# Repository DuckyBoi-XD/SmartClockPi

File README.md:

A Raspberry Pi Zero 2 W based smart clock with touchscreen display, environmental sensing, and internet weather integration.

## KiCad Stuff

This project uses KiCad for PCB design. The files are located in the `PCB/` directory. You can open them with KiCad to view the schematics and PCB layout. These are the screenshots of the PCB and schematics:

### PCB Design

### PCB rendering

### Schematics

## Sketch

## CAD (case design)

## BOM (table format)

| Component | Description | Quantity | Link | Price | Shipping | Est. price (exl. GST) | Est. price (inc. GST) |
|-----------|-------------|----------|------|-------|----------|------------------------|------------------------|
| Raspberry Pi Zero 2 W | Main controller/computer of the project | 1 | https://www.aliexpress.com/item/1005007899652009.html | $15.00 | $0.00 | $15.00 | $17.25 |
| ILI9488 3.5" SPI TFT Touchscreen | 480x320 pixel color LCD with resistive touch input, using SPI interface; displays the clock and all UI elements. | 1 | https://www.aliexpress.com/item/1005007096645415.html | $12.34 | $0.00 | $12.34 | $14.19 |
| DHT22 Sensor | provides indoor environmental readings | 1 | https://www.aliexpress.com/item/32759901711.html | $2.05 | $0.00 | $2.05 | $2.36 |
| 1x14 Pin Socket Header | Single-row, female 2.54mm pitch header; connects the TFT display module to the PCB. | 1 (pack of 10, use 1) | https://www.aliexpress.com/item/4001198421663.html | $1.99 | $0.00 | $1.99 | $2.29 |
| 1x6 Pin Socket Header | Single-row, female 2.54mm pitch header; connects the DAC to the PCB. | 1 (pack of 10, use 1) | https://www.aliexpress.com/item/4001198421663.html | $1.70 | $0.00 | $1.70 | $1.96 |
| 1x6 Pin Socket Header Right angled | Single-row, female 2.54mm pitch, right angle header; connects the RTC module to the PCB. | 1 (pack of 5, use 1) | https://www.aliexpress.com/item/1005008210852764.html | $1.64 | $0.00 | $1.64 | $1.89 |
| 1x4 Pin Socket Header | Single-row, female 2.54mm pitch header; connects the DHT22 to the PCB. | 1 (pack of 10, use 1) | https://www.aliexpress.com/item/4001198421663.html | $1.69 | $0.00 | $1.69 | $1.94 |
| Photoresistor | for automatic display brightness adjustment. 5528 | 1 (pack of 50, use 1) | https://www.aliexpress.com/item/1005002145052802.html | $1.66 | $1.68 | $3.34 | $3.84 |
| MCP3008 (DIP) | 8-channel, 10-bit ADC with SPI interface; reads analog sensors like photoresistors. | 3 (use 1) | https://www.digikey.co.nz/en/products/detail/microchip-technology/MCP3008-I-P/319422 | $9.36 | $0.00 | $9.36 | $10.76 |
| DS3231 RTC (module) | Real-time clock module with battery backup; keeps accurate time when Pi is powered off (or when my internet connection dies) | 1 | https://www.aliexpress.com/item/1005008172587774.html | $1.70 | $0.00 | $1.70 | $1.96 |
| DIP-16 IC socket | For MCP3008 (DIP) | 1 (pack of 10, use 1) | https://www.aliexpress.com/item/1005009030108697.html | $0.60 | $1.63 | $2.23 | $2.56 |
| LIR3032 cell | 3.6V Lithium Battery Rechargeable Battery | 1 (pack of 2, use 1) | https://www.aliexpress.com/item/1005009124669879.html | $7.17 | $0.00 | $7.17 | $8.25 |
| micro-USB port | Power input | 5 (use 1) | https://www.digikey.co.nz/en/products/detail/amphenol-cs-fci/10118193-0001LF/2785388 | $2.15 | $0.00 | $2.15 | $2.47 |
| USB-A port | Power output (from battery charger) | 5 (use 1) | https://www.digikey.co.nz/en/products/detail/gct/USB1046-GF-0190-L-B-A/10649632 | $3.65 | $0.00 | $3.65 | $4.20 |
| 18650 Lithium Battery Charger | 5V 2.4A Dual USB OUT | 1 (pack of 2, use 1) | https://www.aliexpress.com/item/1005006839030660.html | $6.77 | $0.00 | $6.77 | $7.79 |
| microSD card | 64GB | 2 (use 1) | https://www.digikey.co.nz/en/products/detail/raspberry-pi/SC1629/24627140 | $12.98 | $0.00 | $12.98 | $14.93 |
| Diode | 1N4001 | 100 | https://www.digikey.co.nz/en/products/detail/diotec-semiconductor/1N4001/13164614 | $4.66 | $0.00 | $4.66 | $5.36 |
| USB speaker |  | 1 | https://www.aliexpress.com/item/1005007586786674.html | $4.52 | $8.20 | $12.72 | $14.63 |
| **TOTAL** |  |  |  |  |  | **$103.14** | **$118.61** |

## Why I Made This

I wanted a smart clock that could display the time, date, indoor temperature, humidity, and outdoor weather conditions. I also wanted it to have a touchscreen interface for easy interaction. The Raspberry Pi Zero 2 W was chosen for its compact size and sufficient processing power for this project.

"Why don't you just buy a pre-made smart clock?" you might ask. Well, I wanted to learn more about PCB layout/designing. This project is a great way to "exercise" while creating something useful for myself.

Also, I wanted to make it modular so I can easily swap out components or add new features in the future. The custom PCB design allows for easy connections and modifications.

## Features

### Display & Interface

- **3.5" ILI9488 SPI TFT Touchscreen** (480x320 pixels)
- Resistive touch input for UI
- Large, clear font display for time and date
- Automatic brightness adjustment via photoresistor (TO-DO, once I get the parts)

### Environmental Monitoring

- **DHT22 Sensor** for indoor temperature, humidity readings
- Real-time sensor data updates

### Weather Integration

- Internet weather data from wttr.in (Auckland, Half Moon Bay area)
- No API key required
- Displays outdoor temperature, humidity, and weather status
- Update every 10 minutes

### Time & Clock Features

- **DS3231 Real-Time Clock (RTC)** with battery backup
- Maintains accurate time even when Pi is powered off (or when my internet dies)
- Large, readable time display

### Hardware Features

- Custom PCB design with modular connections (so i can unplug and replug the modules)
- Female header pins for easy module connection
- Compact form factor (94.5mm x 67.2mm PCB)

## Hardware Components

Please see [SmartClockPi-bom.csv](SmartClockPi-bom.csv) (Created since this is required for Highway)

## Software Features

- **Python-based application** using:
  - `luma.lcd` for display control
  - `adafruit-circuitpython-bme280` for sensor interface
  - `Pillow` for graphics rendering
- Real-time clock display with large, clear fonts. Need to test if this actually works
- Weather data integration from wttr.in
- Environmental sensor monitoring

## Project Structure

```txt
SmartClockPi/
├── README.md
├── JOURNAL.md                # Development journal with progress updates
├── SmartClockPi-bom.csv      # Bill of Materials
├── PCB/                      # KiCad PCB design files
│   ├── smartclockpi.kicad_pro
│   ├── smartclockpi.kicad_sch
│   ├── smartclockpi.kicad_pcb
│   └── Gerber/               # Manufacturing files
└── [Software files to be added]
```

## Acknowledgements

- Thanks to the Raspberry Pi community for their resources and other stuff.
- A HUGE shoutout to my friend, [@DuckyBoi-XD](https://github.com/DuckyBoi-XD), for designing the case/enclosure for this project, located in the `CAD/` directory.

## License

This project is Free and Open-source, licensed under the GPLv3 license. Feel free to contribute or use it for your own projects!

See [LICENSE](LICENSE) for more details.

---

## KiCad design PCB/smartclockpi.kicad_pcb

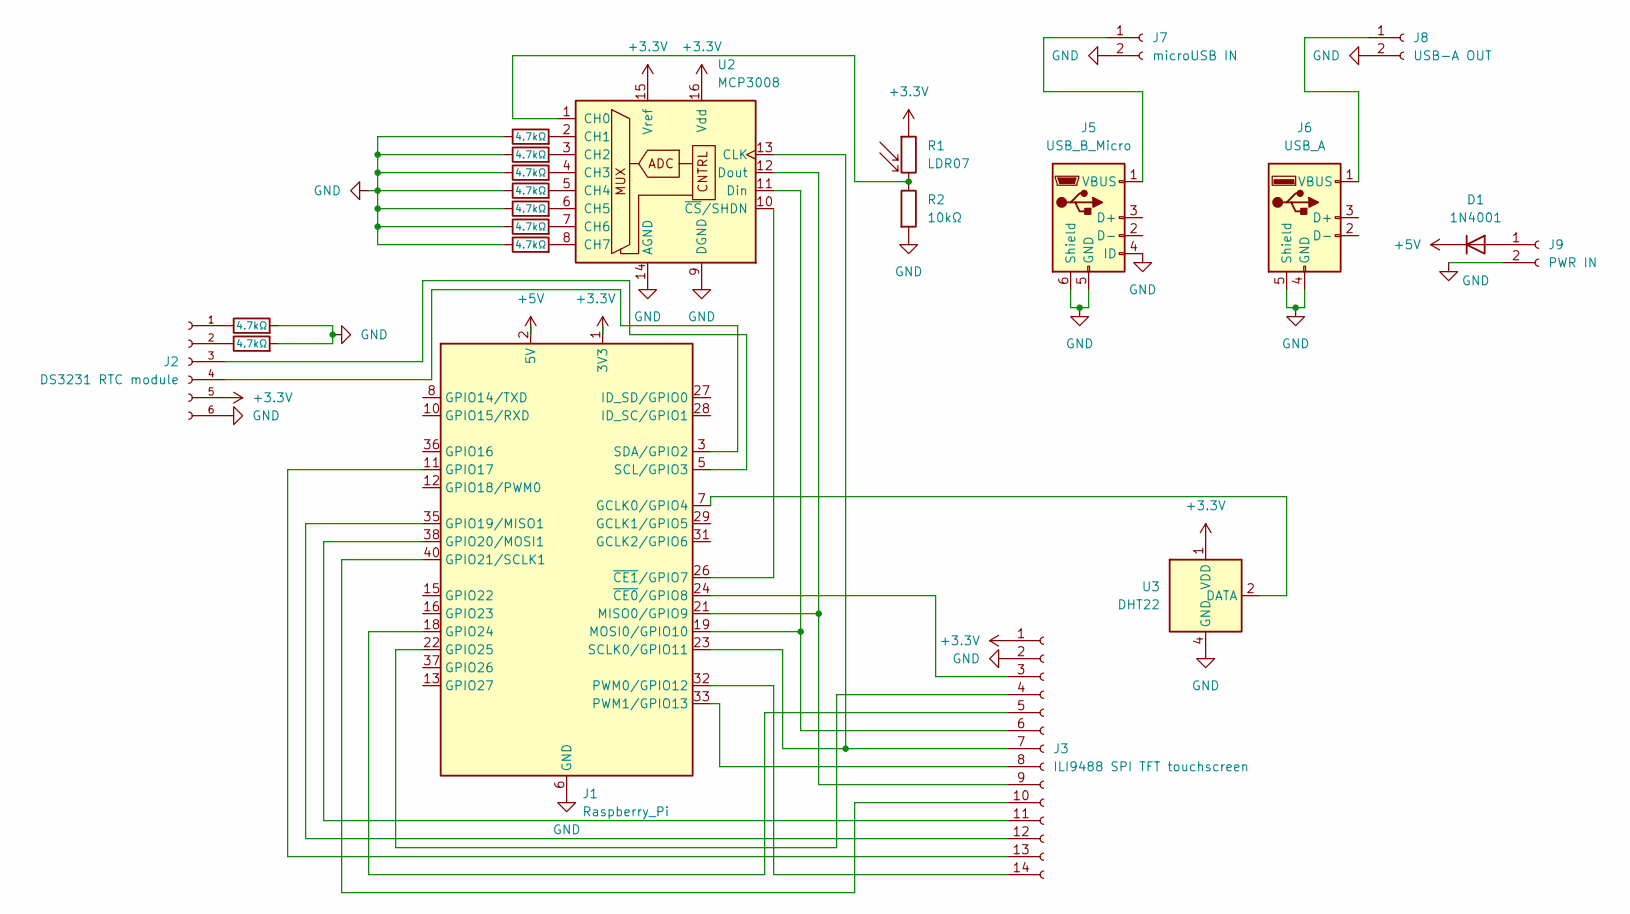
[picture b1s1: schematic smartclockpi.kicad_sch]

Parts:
D1: 1N4001; D_DO-41_SOD81_P10.16mm_Horizontal
J1: Raspberry_Pi; PinHeader_2x20_P2.54mm_Vertical
J2: DS3231 RTC module; PinSocket_1x06_P2.54mm_Horizontal
J3: ILI9488 SPI TFT touchscreen; PinSocket_1x14_P2.54mm_Vertical
J5: USB_B_Micro; USB_Micro-B_Amphenol_10118193-0001LF_Horizontal
J6: USB_A; USB_A_Receptacle_GCT_USB1046
J7: microUSB IN; PinSocket_1x02_P2.54mm_Vertical
J8: USB-A OUT; PinSocket_1x02_P2.54mm_Vertical
J9: PWR IN; PinSocket_1x02_P2.54mm_Vertical
R1: LDR07; R_LDR_5.2x5.2mm_P3.5mm_Horizontal
R2: 10kΩ; R_Axial_DIN0204_L3.6mm_D1.6mm_P5.08mm_Horizontal
R3, R4, R5, R6, R7, R8, R9, R12, R13: 4.7kΩ; R_Axial_DIN0204_L3.6mm_D1.6mm_P5.08mm_Horizontal
U2: MCP3008; DIP-16_W7.62mm_Socket
U3: DHT22; Aosong_DHT11_5.5x12.0_P2.54mm

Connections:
+3.3V: J1.1 (3V3), J1.17 (3V3), J2.5 (VCC), J3.1 (VCC), R1.1, U2.15 (Vref), U2.16 (Vdd), U3.1 (VDD)
+5V: D1.1 (K), J1.2 (5V), J1.4 (5V)
GND: J1.6 (GND), J1.9 (GND), J1.14 (GND), J1.20 (GND), J1.25 (GND), J1.30 (GND), J1.34 (GND), J1.39 (GND), J2.6 (GND), J3.2 (GND), J5.4 (ID), J5.5 (GND), J5.6 (Shield), J6.4 (GND), J6.5 (Shield), J7.2, J8.2, J9.2, R2.2, R3.1, R4.1, R5.1, R6.1, R7.1, R8.1, R9.1, R12.2, R13.2, U2.9 (DGND), U2.14 (AGND), U3.4 (GND)
unnamed: D1.2 (A), J9.1
unnamed: J1.7 (GCLK0/GPIO4), U3.2 (DATA)
unnamed: J1.11 (GPIO17), J3.13 (T_DO)
unnamed: J1.35 (GPIO19/MISO1), J3.12 (T_DIN)
unnamed: J1.38 (GPIO20/MOSI1), J3.11 (T_CS)
unnamed: J1.40 (GPIO21/SCLK1), J3.10 (T_CLK)
unnamed: J1.18 (GPIO24), J3.5 (DC/RS)
unnamed: J1.22 (GPIO25), J3.4 (RESET)
unnamed: J1.21 (MISO0/GPIO9), J3.9 (MISO), U2.12 (Dout)
unnamed: J1.19 (MOSI0/GPIO10), J3.6 (MOSI), U2.11 (Din)
unnamed: J1.32 (PWM0/GPIO12), J3.14 (T_IRQ)
unnamed: J1.33 (PWM1/GPIO13), J3.8 (LED)
unnamed: J1.23 (SCLK0/GPIO11), J3.7 (SCK), U2.13 (CLK)
unnamed: J1.5 (SCL/GPIO3), J2.3 (SCL)
unnamed: J1.3 (SDA/GPIO2), J2.4 (SDA)
unnamed: J1.24 (~CE0/GPIO8), J3.3 (CS)
unnamed: J1.26 (~CE1/GPIO7), U2.10 (~CS/SHDN)
unnamed: J2.1 (32K), R12.1
unnamed: J2.2 (SQW), R13.1
unnamed: J5.1 (VBUS), J7.1
unnamed: J6.1 (VBUS), J8.1
unnamed: R1.2, R2.1, U2.1 (CH0)
unnamed: R3.2, U2.2 (CH1)
unnamed: R4.2, U2.3 (CH2)
unnamed: R5.2, U2.4 (CH3)
unnamed: R6.2, U2.5 (CH4)
unnamed: R7.2, U2.6 (CH5)
unnamed: R8.2, U2.7 (CH6)
unnamed: R9.2, U2.8 (CH7)

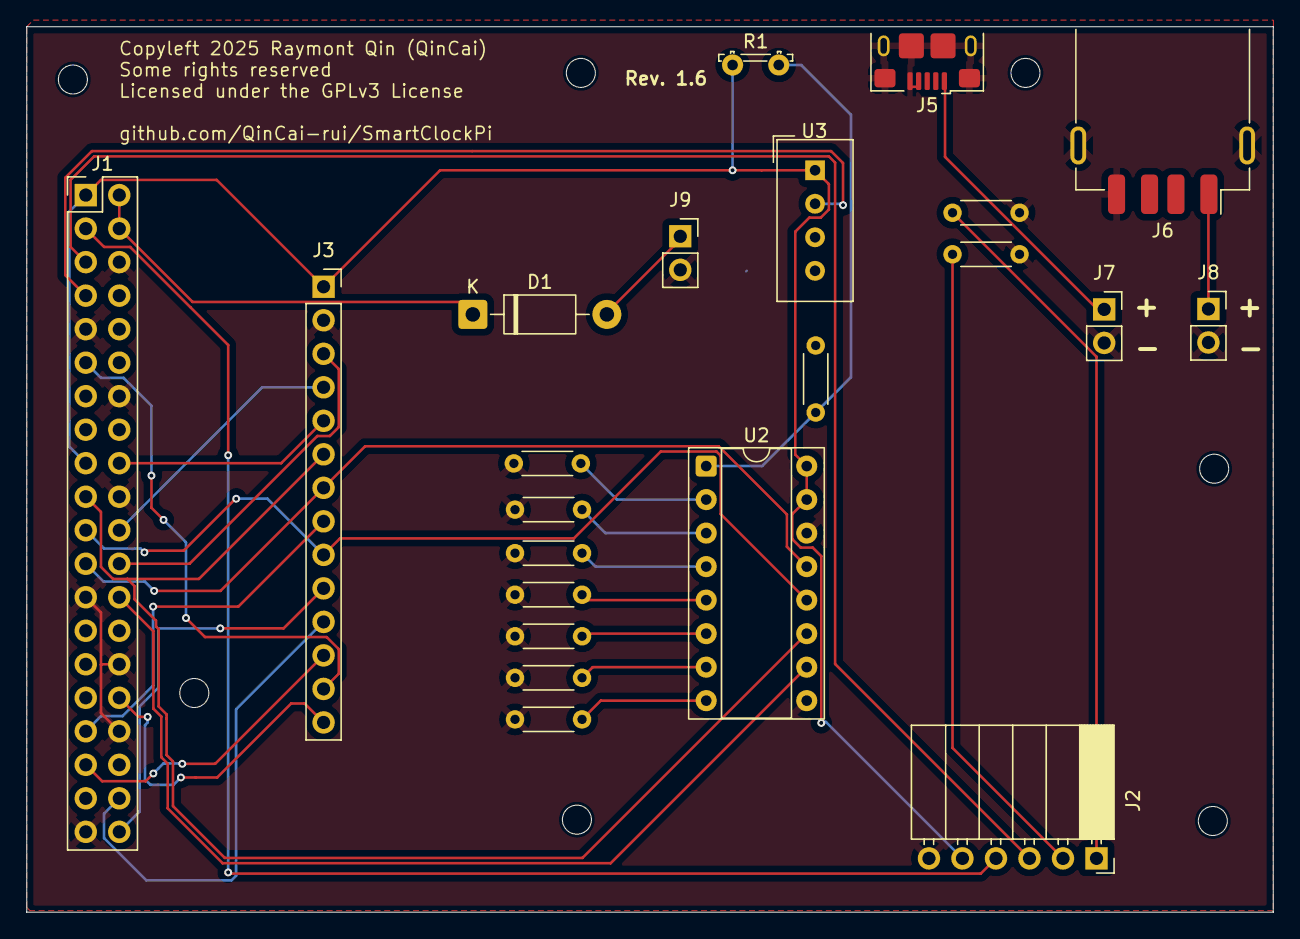
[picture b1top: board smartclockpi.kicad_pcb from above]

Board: 2 copper layers, 94.5 x 67.1 mm, 22 parts (0 on the bottom side), 32 nets.

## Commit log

2025-06-09 very basic clock
2025-06-10 added real weather support
2025-06-10 update journal about today's work
2025-06-10 another update-working on schematics
2025-06-13 add schematics and pcb
2025-06-13 add gitignore file
2025-06-13 update gitignore
2025-06-13 remove files
2025-06-14 update time spendings
2025-06-16 finallise pcb. spent toooo much time on this...
2025-06-16 quick update. not done yet
2025-06-16 finishing update 7
2025-06-17 update pcb
2025-06-17 update pcb. idk what i did
2025-06-18 add in usb ports
2025-06-18 add 3d model of PCB
2025-06-18 add gerber files
2025-06-19 add BOM
2025-06-24 update pcb and stuff
2025-06-25 Create LICENSE
2025-06-25 I hate emojis ty
2025-06-25 bye bye whitespaces
2025-06-26 update journal
2025-06-26 update BOM
2025-06-26 update time
2025-06-26 update images
2025-06-26 lint
2025-06-26 update kicad stuff
2025-06-26 test
2025-06-26 rm test
2025-06-29 add sketch
2025-06-29 add "why i made this"
2025-06-29 oopsies
2025-06-29 add pcb rendering
2025-06-30 update readme to include table format BOM
2025-07-02 modify pcb
2025-07-02 update gerber zip
2025-07-02 fix corrupted file
2025-07-02 update gerber to include drill
2025-07-02 add drl
2025-07-02 update Gerber
2025-07-02 fix resistor positions
2025-07-03 update step file
2025-07-03 fix PCB issues and re-gen everything needed
2025-07-03 fix some DRC errors. regen models
2025-07-03 update footprint for LDR. re-gen models
2025-07-03 add ziped gerbers
2025-07-04 Create CAD
2025-07-06 add backups
2025-07-06 create CAD folder
2025-07-06 rm placeholder
2025-07-06 remove placeholder
2025-07-07 rename CAD files
2025-07-07 add acknoledgements
2025-07-07 oopsies mixed up my projects
2025-07-07 add images of case

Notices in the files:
PCB/smartclockpi.kicad_pcb:
Copyleft 2025 Raymont Qin (QinCai)
